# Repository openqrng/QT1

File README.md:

# QT1
This repository contains sources of the OpenQRNG QT1.

## Description
OpenQRNG QT1 is a 1Mbps open source quantum random number generator compliant with NIST-SP800-22 test suite.
This repository contains:
* Hardware sources (schematic, PCB...)
* Software source
* Documentations (operating manual)

## License

#### Hardware
All hardware is licensed under the CERN-OHL-S v2.

Copyright OpenQRNG 2023.

This source describes Open Hardware and is licensed under the CERN-OHL-S v2.

You may redistribute and modify this documentation and make products using it under the terms of the [CERN-OHL-S v2](https://cern.ch/cern-ohl). This documentation is distributed WITHOUT ANY EXPRESS OR IMPLIED WARRANTY, INCLUDING OF MERCHANTABILITY, SATISFACTORY QUALITY AND FITNESS FOR A PARTICULAR PURPOSE. Please see the CERN-OHL-S v2 for applicable conditions

#### Software
Copyright (C) 2023 OpenQRNG

All software is free software: you can redistribute it and/or modify it under the terms of the GNU General Public License as published by the Free Software Foundation, version 3.

This program is distributed in the hope that it will be useful, but WITHOUT ANY WARRANTY; without even the implied warranty of MERCHANTABILITY or FITNESS FOR A PARTICULAR PURPOSE. See the GNU General Public License for more details.

You should have received a copy of the GNU General Public License along with this source. If not, see https://www.gnu.org/licenses/.

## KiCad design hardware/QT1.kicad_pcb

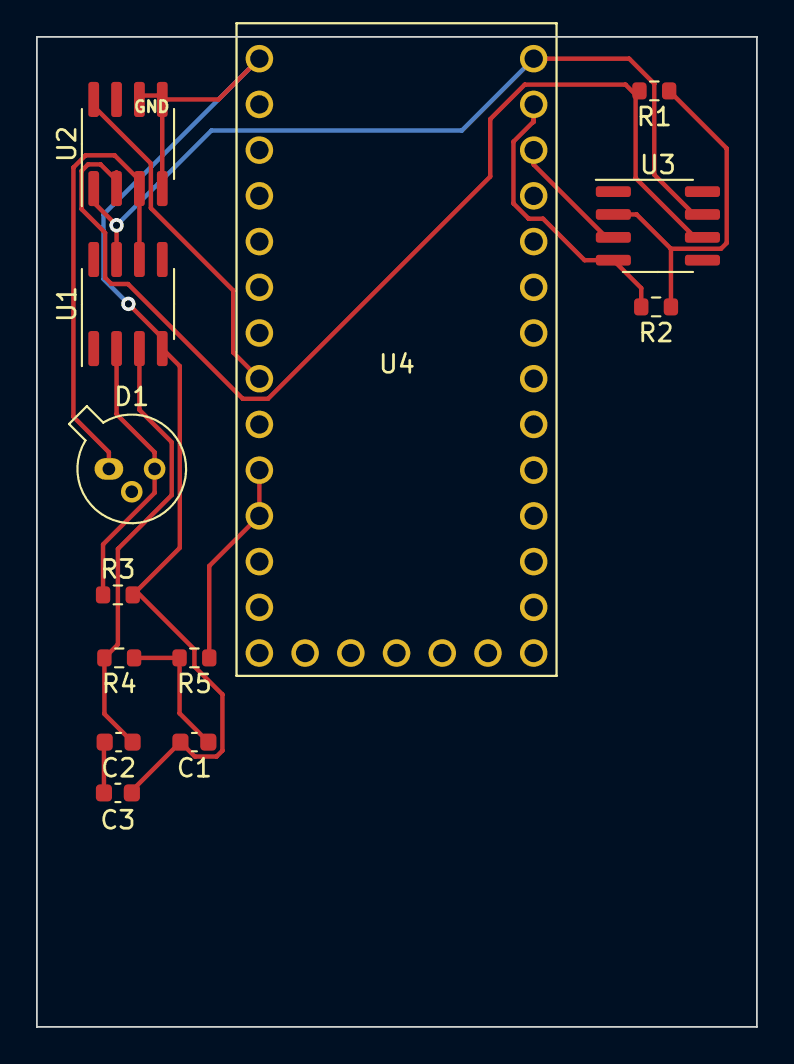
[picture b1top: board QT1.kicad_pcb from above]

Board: 2 copper layers, 40.0 x 55.0 mm, 13 parts (0 on the bottom side), 13 nets.

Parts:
C1: 50pF; C_0603_1608Metric
C2, C3: 75pF; C_0603_1608Metric
D1: AEY22; TO-18-3
R1: 110; R_0603_1608Metric
R2: 1k; R_0603_1608Metric
R3: 680; R_0603_1608Metric
R4, R5: 500; R_0603_1608Metric
U1: TLE2141CD; SOIC-8_3.9x4.9mm_P1.27mm
U2: AD8561ARZ; SOIC-8_3.9x4.9mm_P1.27mm
U3: MCP601-xSN; SOIC-8_3.9x4.9mm_P1.27mm
U4: Teensy 4.0; MODULE_DEV-15583

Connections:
+3.3V: U3.3 (+), U4.3.3V_2
+5V: U1.7 (V+), U2.1 (V+), U3.7 (V+), U4.VIN
GND1: C1.2, C3.2, R3.2, U1.4 (V-), U2.4 (V-), U2.5 (LATCH), U2.6 (GND), U4.G1
GND3: R2.2, U3.4 (V-), U4.G3
unnamed: C1.1, R4.1, R5.2
unnamed: C2.2, C3.1
unnamed: D1.1 (A), U1.6, U2.3 (-)
unnamed: D1.3 (K), R3.1, U1.2 (-)
unnamed: R5.1, U4.8, U4.9
unnamed: C2.1, R4.2, U1.3 (+)
unnamed: R1.2, U2.2 (+), U3.6
unnamed: U2.8 (~Q), U4.6
unnamed: R1.1, R2.1, U3.2 (-)

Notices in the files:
hardware/QT1.kicad_pcb:
Licensed under CERN-OHL-S v2.
